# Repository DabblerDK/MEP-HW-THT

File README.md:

# MEP-HW-THT v1.10
Multipurpose Expansion Port (MEP) Through-Hole Technology (THT) Hardware for OSGP Smart Meters in Denmark

---
# This hardware will not be updated any further as I no longer have access to a NES Smart Meter. Read more here: https://www.dabbler.dk/index.php/2023/10/31/echelon-nes-smart-meters-probably-our-final-post-on-this-topic/
---

This is the repository holding the Thrugh-Hole Technology (THT) Hardware for OSGP Smart Meters (i.e. Echelon or NES) in Denmark.
The scematics can be use in other countries too if you gain access to the Multipurpose Expansion Port (MEP) terminals.
Please:
- see https://github.com/OSGP-Alliance-MEP-and-Optical for further hardware specifiactions of these meters.
- see https://www.dabbler.dk for further information about this hardware project

Version 1.10 is THT and version 2.00 is SMD. The two versions share schematics and are 100% compatible. They uses the same software and have the exact same functionality - only the component technology has changed.

Notes:
- The Gerber files has been generated acording to [JLCPCBs](https://jlcpcb.com/) specifications.
- We have not been able to source the correct MEP connector, so please note that the pin-numbers does NOT corespond to the pin numbers in the official documentation. Also you should NOT insert the 2x3 pin headers all the way into the PCB (the pins should be aligned with the PCB back side).
- The ESP32 can be programmed "on board" using the J5 connector. We usually don't put headers on that one, but simply insert the pins of a FTDI232 directly into the holes. WARNING: Some FTDI232's supply 5v EVEN when they are jumped to 3.3v. Don't use those - they'll fry your ESP32!
- Debug information from the software are written on the serial out on J5. Remember it is 3.3v and if you use a FTDI232, please only connect GND, TXD and RXD during normal operation (i.e. when the module is connected to a meter)
- The Schematic for the THT and the SMD versions are currently the same, but they might branch in the future
- J7 have two functions: before "on board" programming of the ESP32 a jumper must be set between ESP_PROGRAM and GND (pin 1 and 2) and the power jumper between pin 3 and 4 must be removed
- WARNING: Remove all jumpers from J7 before adjusting the buck converter voltage to 3.4-3.5v. When done set a jumper between pin 3 and 4 for nomal operation.
- The buck converter must be mounted without pin headers, i.e. flush to the PCB. Just put solder blobs in the holes and use additional heat for a good connection. The module will not fit in the meter if pin headers are used!

Troubleshooting PCBs with fake MAX3232:
- If you don't have R3 populated (ESP32 controlled power for the MAX3232 - see below), you will be able to measure the set voltage from the buck converter on one pin, and the actual power suppliedby the ESP32 on the other. The ESP32 cannot supply much power, so you'll measure a voltage far below the 3.3v required by the MAX3232, the MAX3232 won't work and your ESP32 will get hot. Don't run in that configuration for long - replace your MAX3232 with a working one!
- If you don't have R3 populated (ESP32 controlled power for the MAX3232 - see below), remove the J7 jumper completely and measure resistance between the ESP32 pin 1 and 2, you'll see a short if your ESP32 is fried
- If you have R3 populated (but not R4 populated), you can measure if your ESP32 is fried by removing J7 and the MAX3232 chip
- You can check if your MAX3232 chip is fried or fake by measuring resistance between pin 15 and 16 when it is not in the board. It should be above 15Kohm - possible 30-40Kohm. Warning: It might still be a fake if it is, but at least it is not shorting anything then (see the first point in this section

Bill of Materials:
| Component | Value | Type | Note |
| ------------- | ------------- | ------------- | ------------- |
| R1-R2 | 10K ohm | | |
| R3-R7 | 0 ohm or wire | | Mount either R3 (permanent) or R4 (ESP32 controlled, recommended) depending on how you will power your MAX3232. See https://www.dabbler.dk/index.php/2022/04/03/echelon-nes-smart-meters-dabbling-the-hardware-v1-10-and-v2-00/. Do not use the J7 header pins for these. |
| D1 | 1N4007 | | Square solder pad should be aligned towards the marking on the diode |
| C1-C5 | 100nF | Non-polarized | |
| U1 | MAX3232 and socket | DIP-16 | 3.3v version (warning: lots of fake chips out there - we recommend using a socket). IMPORTANT: Make sure to tim the pins on the back of the PCB so they stay clear of the J6 connector pins! |
| U2 | ESP32-wroom-32e | 16MB recommended but currently NOT required | We have not experienced any thermal issues so we do not solder the middle thermal pad. Just make sure the ESP32 is flush with the PCB
| J1-J4 | DC-DC Buck converter | | i.e. https://www.ebay.com/itm/264731212329. The VIN- corner should be aligned towards J7 |
| J6 | 2x3 Horizontal pin header | 2.54mm | IMPORTANT: Do not insert this pin header fully in the PCB. The pins should be soldered exactly flush with the PCB surface on the soldering side of the PCB to fit the connector in the meter! i.e. https://www.ebay.com/itm/253023279430.<br>2024-03-12 A better option is to use the correct connector - you will find it on AliExpress here https://www.aliexpress.com/item/1005002409430150.html |
| J7 | 2x2 Vertical pin header | 2.54mm | You will need one jumper for these: If set horizontally between the two pins next to the PCB edge it is in programming mode (use FTDI232 board connected to J5 to program). If set horizontally between the two pins just above the horizontal C5 capacitor it is in normal operation. Remove jumper completely while adjusting the Buck converter (no power will then be supplied to chips) |

Pictures of the populated PCB:

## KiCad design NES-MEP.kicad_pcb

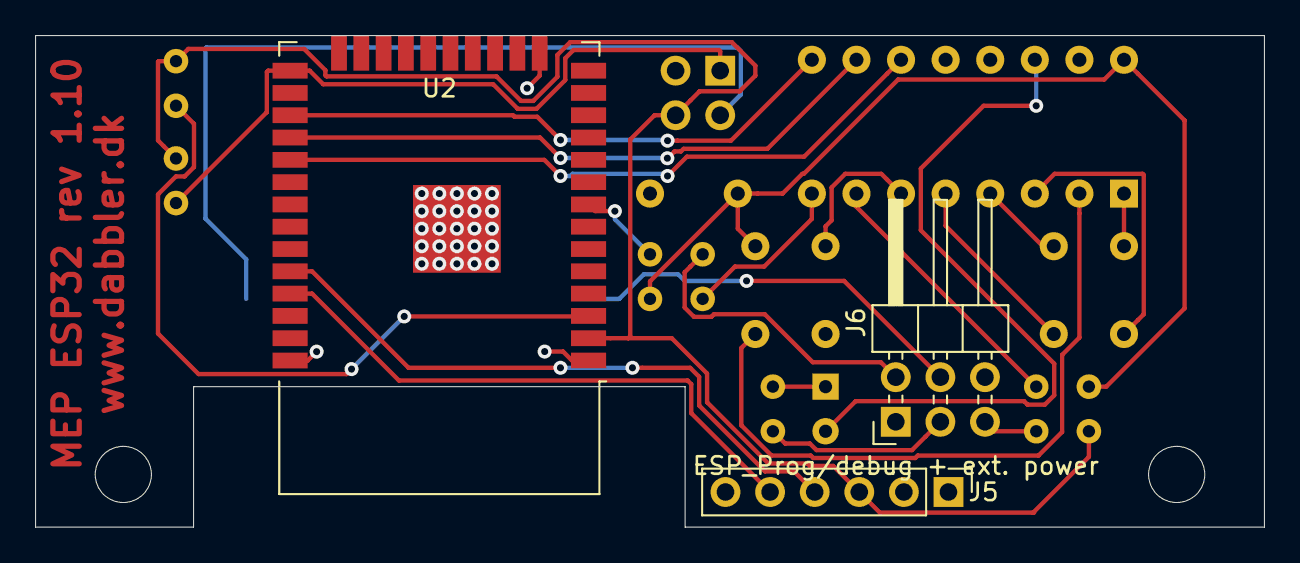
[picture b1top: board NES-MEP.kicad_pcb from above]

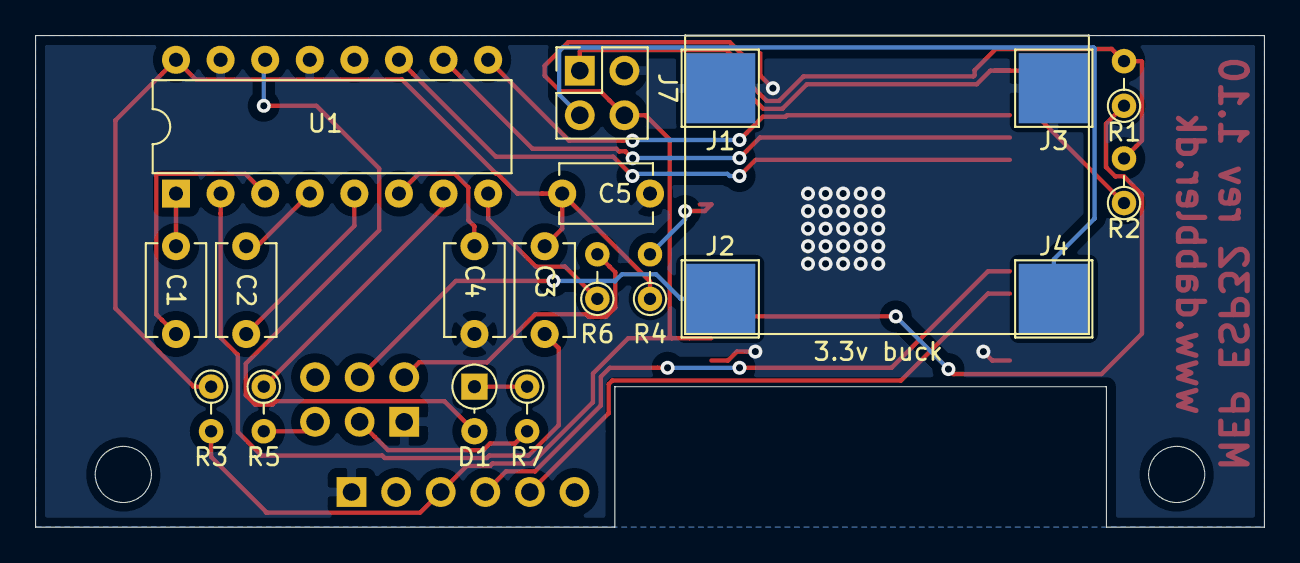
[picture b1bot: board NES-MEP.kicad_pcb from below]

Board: 2 copper layers, 70.0 x 28.0 mm, 22 parts (19 on the bottom side), 26 nets.

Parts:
C1, C2, C3, C4, C5: 100nF; C_Disc_D5.1mm_W3.2mm_P5.00mm
D1: 1N4007; D_DO-34_SOD68_P2.54mm_Vertical_AnodeUp
J1: Buck GND input; TestPoint_Pad_4.0x4.0mm
J2: Buck +24v input; TestPoint_Pad_4.0x4.0mm
J3: Buck GND output; TestPoint_Pad_4.0x4.0mm
J4: Buck +3v3 output; TestPoint_Pad_4.0x4.0mm
J5: ESP_Prog/debug + ext. power; PinHeader_1x06_P2.54mm_Vertical
J6: NES Meter MEP; PinHeader_2x03_P2.54mm_Horizontal
J7: Program/Enable Meter Power; PinHeader_2x02_P2.54mm_Vertical
R1, R2: 10K; R_Axial_DIN0204_L3.6mm_D1.6mm_P2.54mm_Vertical
R3, R4, R5, R6, R7: 0; R_Axial_DIN0204_L3.6mm_D1.6mm_P2.54mm_Vertical
U1: MAX3232; DIP-16_W7.62mm
U2: ESP32-WROOM-32

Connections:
+3V3: J5.3, J7.4, R1.2, R2.2, R3.2, U2.2
+24V: J2.1, J6.4
ENABLE: J6.3, R7.2
ENABLE_TTL: U1.11, U2.29
ESP_PROGRAM: J7.1, R2.1, U2.25
ESP_RXD0: J5.4, U2.34
ESP_TXD0: J5.5, U2.35
GND: C4.1, C5.2, J1.1, J3.1, J5.1, J6.1, J7.2, U1.13, U1.15, U2.1, U2.15, U2.38, U2.39
unnamed: C1.1, U1.1
unnamed: C1.2, U1.3
unnamed: C2.1, U1.4
unnamed: C2.2, U1.5
unnamed: C3.1, C5.1, R3.1, R4.1, U1.16
unnamed: C3.2, U1.2
unnamed: C4.2, U1.6
unnamed: D1.1, R7.1
unnamed: D1.2, U1.14
unnamed: J4.1, J7.3
unnamed: R1.1, U2.3
unnamed: R5.1, U1.7
unnamed: R6.1, U1.8
RS3232_ENABLE: R4.2, U2.8
RXD: J6.2, R6.2
RXD2_TTL: U1.9, U2.27
TXD: J6.5, R5.2
TXD2_TTL: U1.10, U2.28

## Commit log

2022-07-25 Corrected URL
2022-07-25 Adding more hardware notes
2022-07-25 Added yet another note
2022-07-25 Added a note
2022-09-08 Update README.md
    Added description on when to use R3 and R4
2022-09-10 Note about soldering the MEP connector correctly and trimming the socket pins
2022-09-17 Update README.md
    Added a section for "WARNING: Troubleshooting PCBs with fake MAX3232"
2022-09-17 Update README.md
    Improved the "Troubleshooting PCBs with fake MAX3232" section
2022-10-05 Assembly clarifications
2022-11-13 Update README.md
    J7 description of jumper configuration
2022-11-19 Update README.md
    3.4-3.5v seems to work fine for the ESP32, so no need to push it...
2023-01-21 Update README.md
    Explain that v1.1 and v2.0 have same functionality. 1.1 is just THT, while 2.0 is SMD
2023-01-21 Update README.md
    typo
2023-01-29 Added images
    Added images
2023-01-30 Update readme
    Added note about us not soldering the thermal pad of the ESP32
2024-03-12 Update README.md
    Added info on the correct MEP connector
